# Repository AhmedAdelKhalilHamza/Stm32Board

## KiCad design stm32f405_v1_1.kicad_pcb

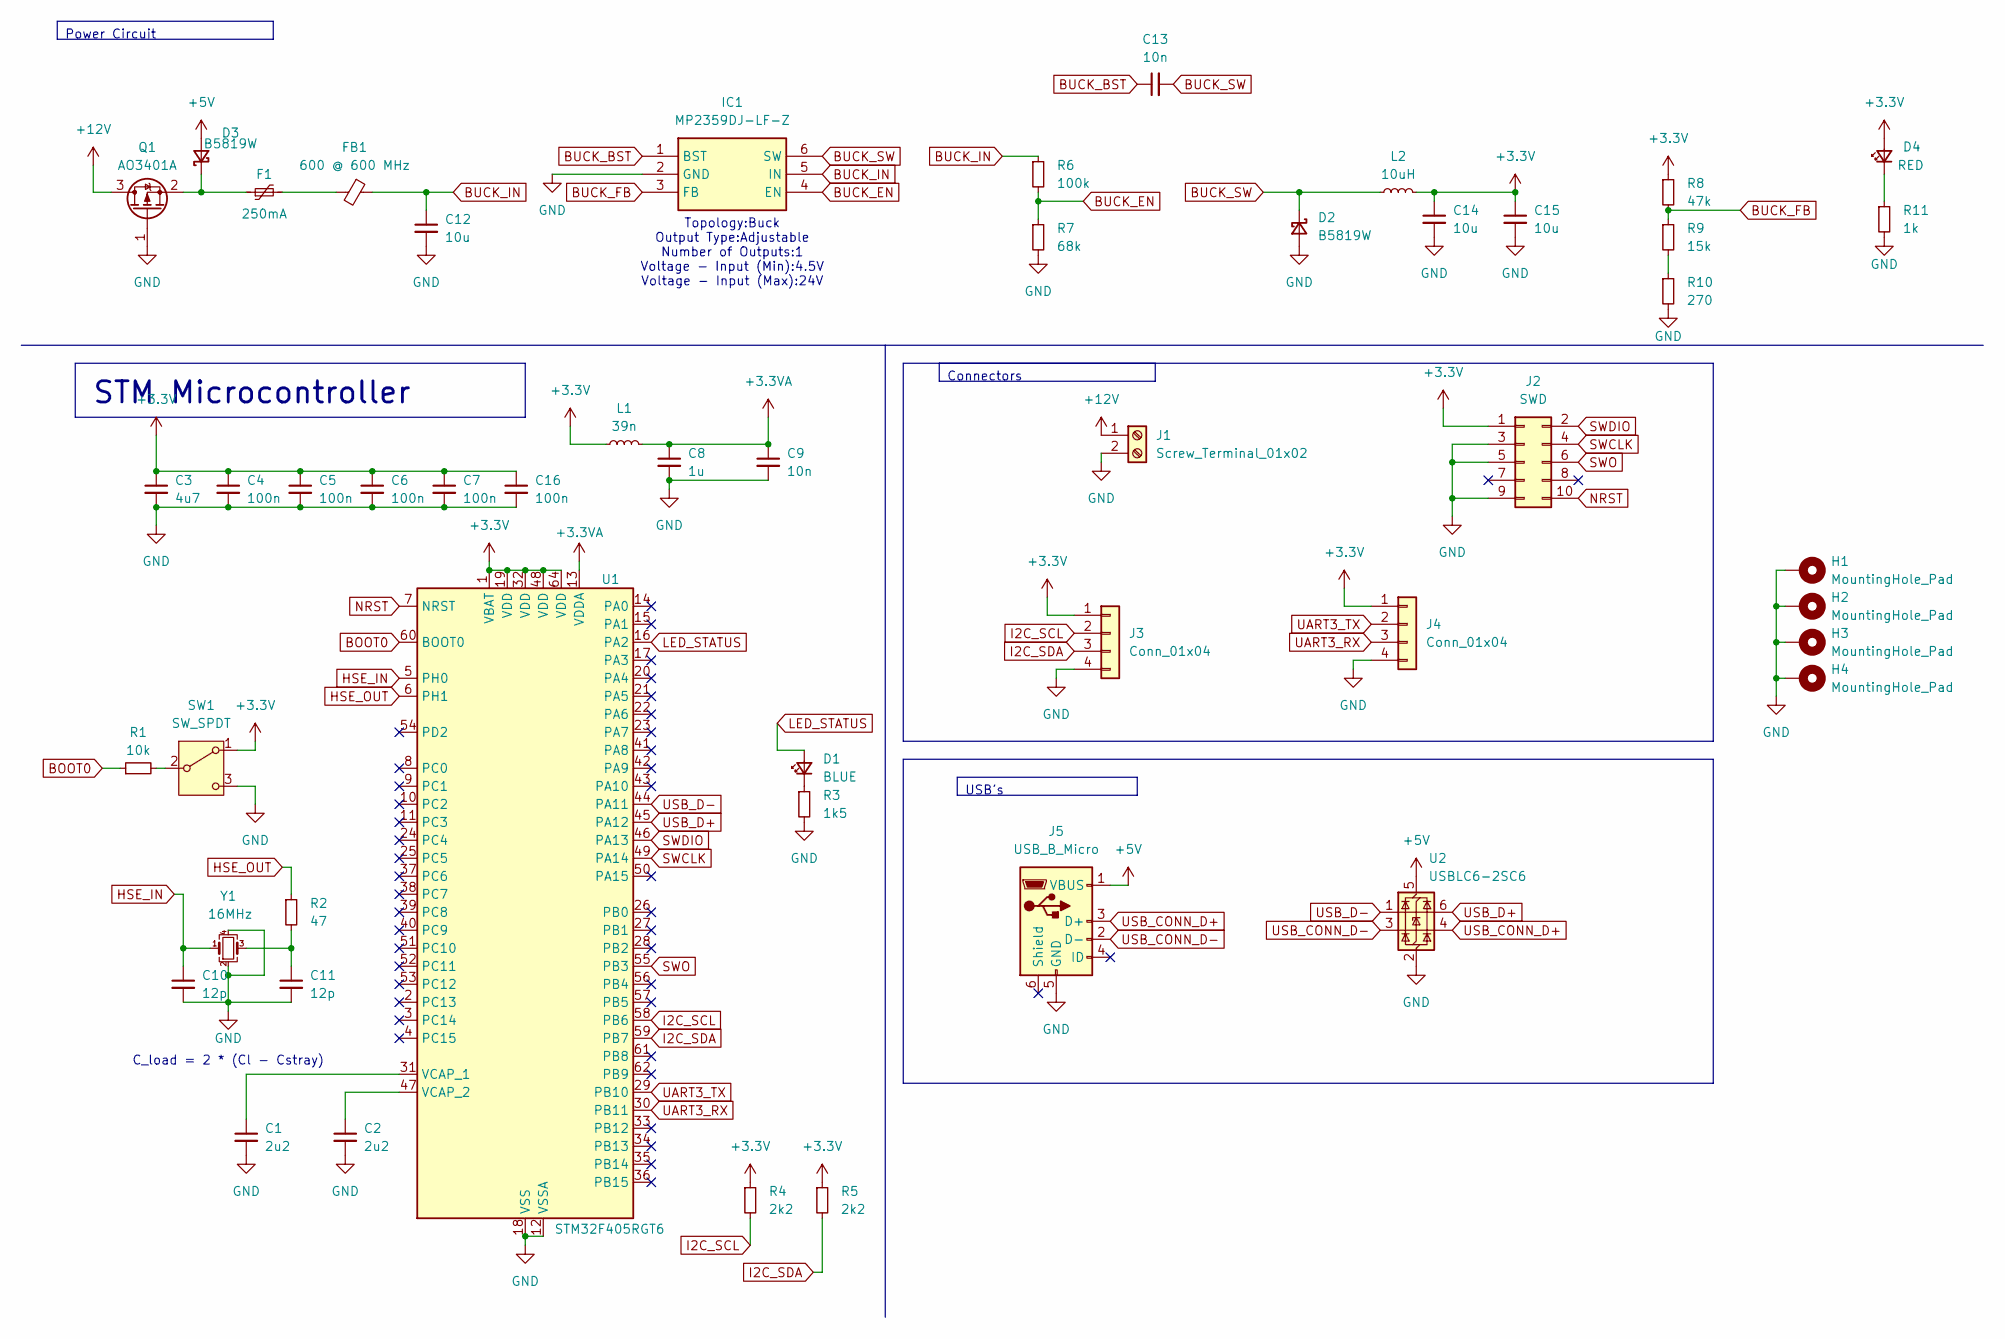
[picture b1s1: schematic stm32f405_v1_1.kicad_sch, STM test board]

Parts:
C1, C2: 2u2; C_0603_1608Metric; DigiKey# 1276-1134-1-ND
C3: 4u7; C_0603_1608Metric; DigiKey# 1276-1045-1-ND
C4, C5, C6, C7, C16: 100n; C_0402_1005Metric; DigiKey# 2679-AGC0402X7R160-104KNP-CT-ND
C8: 1u; C_0402_1005Metric; DigiKey# 490-13339-1-ND
C9: 10n; C_0402_1005Metric; DigiKey# 490-1313-1-ND
C10, C11: 12p; C_0402_1005Metric; DigiKey# 490-11190-1-ND
C12, C14, C15: 10u; C_1206_3216Metric; DigiKey# 1276-3105-1-ND
C13: 10n; C_0603_1608Metric; DigiKey# 399-C0603C103K9RAC7867CT-ND
D1: BLUE; LED_0603_1608Metric; DigiKey# 732-12013-1-ND
D2, D3: B5819W; D_SOD-123; DigiKey# 1727-7326-1-ND
D4: RED; LED_0603_1608Metric; DigiKey# 732-4978-1-ND
F1: 250mA; Fuse_1206_3216Metric; DigiKey# SF-1206HH25M-2CT-ND
FB1: 600 @ 600 MHz; L_0805_2012Metric; DigiKey# 1934-1435-1-ND
H1, H2, H3, H4: MountingHole_Pad; MountingHole_4.3mm_M4_Pad_Via
IC1: MP2359DJ-LF-Z; SOT95P280X100-6N; Manufacturer_Part_Number MP2359DJ-LF-Z; DigiKey# 1589-1889-1-ND
J1: Screw_Terminal_01x02; TerminalBlock_Phoenix_PT-1,5-2-3.5-H_1x02_P3.50mm_Horizontal; DigiKey# 732-10955-ND
J2: SWD; PinSocket_2x05_P1.27mm_Vertical_SMD; DigiKey# 1528-5327-ND
J3, J4: Conn_01x04; Molex_KK-254_AE-6410-04A_1x04_P2.54mm_Vertical; Mouser Part Number 538-171856-4004
J5: USB_B_Micro; USB_Mini-B_Wuerth_65100516121_Horizontal; DigiKey# 732-2109-1-ND
L1: 39n; L_0402_1005Metric; DigiKey# 2035-1057-1-ND
L2: 10uH; L_Sunlord_MWSA0518S; DigiKey# 3442-MWSA0518S-100MTCT-ND
Q1: AO3401A; SOT-23; DigiKey# 785-1001-1-ND
R1: 10k; R_0402_1005Metric; DigiKey# 311-10KJRCT-ND
R2: 47; R_0402_1005Metric; DigiKey# RMCF0402JT47R0CT-ND
R3: 1k5; R_0603_1608Metric; DigiKey# P1.5KDCCT-ND
R4, R5: 2k2; R_0402_1005Metric; DigiKey# P2.20KLCT-ND
R6: 100k; R_0603_1608Metric; DigiKey# 311-100KHRCT-ND
R7: 68k; R_0603_1608Metric; DigiKey# P68.0KHCT-ND
R8: 47k; R_0603_1608Metric; DigiKey# P47.0KHCT-ND
R9: 15k; R_0603_1608Metric; DigiKey# P15KDBCT-ND
R10: 270; R_0603_1608Metric; DigiKey# 311-270GRCT-ND
R11: 1k; R_0603_1608Metric; DigiKey# RMCF0603FT1K00CT-ND
SW1: SW_SPDT; SW_SPDT_PCM12; DigiKey# 401-2016-1-ND
U1: STM32F405RGT6; LQFP-64_10x10mm_P0.5mm; DigiKey# 497-11767-ND
U2: USBLC6-2SC6; SOT-23-6; DigiKey# 497-5235-1-ND
Y1: 16MHz; Crystal_SMD_3225-4Pin_3.2x2.5mm; DigiKey# 4983-12.88722CT-ND

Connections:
+3.3V: C3.1, C4.1, C5.1, C6.1, C7.1, C14.1, C15.1, C16.1, D4.2 (A), J2.1, J3.1, J4.1, L1.1, L2.2, R4.1, R5.1, R8.1, SW1.1 (A), U1.1 (VBAT), U1.19 (VDD), U1.32 (VDD), U1.48 (VDD), U1.64 (VDD)
+3.3VA: C8.1, C9.1, L1.2, U1.13 (VDDA)
+5V: D3.2 (A), J5.1 (VBUS), U2.5 (VBUS)
+12V: J1.1, Q1.3 (D)
BOOT0: R1.1, U1.60 (BOOT0)
BUCK_BST: C13.1, IC1.1 (BST)
BUCK_EN: IC1.4 (EN), R6.2, R7.1
BUCK_FB: IC1.3 (FB), R8.2, R9.1
BUCK_IN: C12.1, FB1.1, IC1.5 (IN), R6.1
BUCK_SW: C13.2, D2.1 (K), IC1.6 (SW), L2.1
GND: C1.2, C2.2, C3.2, C4.2, C5.2, C6.2, C7.2, C8.2, C9.2, C10.2, C11.2, C12.2, C14.2, C15.2, C16.2, D2.2 (A), H1.1, H2.1, H3.1, H4.1, IC1.2 (GND), J1.2, J2.3, J2.5, J2.9, J3.4, J4.4, J5.5 (GND), Q1.1 (G), R3.2, R7.2, R10.2, R11.2, SW1.3 (C), U1.12 (VSSA), U1.18 (VSS), U1.63 (VSS), U2.2 (GND), Y1.2, Y1.4
HSE_IN: C10.1, U1.5 (PH0), Y1.1
HSE_OUT: R2.1, U1.6 (PH1)
I2C_SCL: J3.2, R4.2, U1.58 (PB6)
I2C_SDA: J3.3, R5.2, U1.59 (PB7)
LED_STATUS: D1.2 (A), U1.16 (PA2)
NRST: J2.10, U1.7 (NRST)
unnamed: C11.1, R2.2, Y1.3
unnamed: D1.1 (K), R3.1
unnamed: D3.1 (K), F1.1, Q1.2 (S)
unnamed: D4.1 (K), R11.1
unnamed: F1.2, FB1.2
unnamed: R9.2, R10.1
unnamed: R1.2, SW1.2 (B)
unnamed: C1.1, U1.31 (VCAP_1)
unnamed: C2.1, U1.47 (VCAP_2)
SWCLK: J2.4, U1.49 (PA14)
SWDIO: J2.2, U1.46 (PA13)
SWO: J2.6, U1.55 (PB3)
UART3_RX: J4.3, U1.30 (PB11)
UART3_TX: J4.2, U1.29 (PB10)
USB_CONN_D+: J5.3 (D+), U2.4 (I/O2)
USB_CONN_D-: J5.2 (D-), U2.3 (I/O2)
USB_D+: U1.45 (PA12), U2.6 (I/O1)
USB_D-: U1.44 (PA11), U2.1 (I/O1)

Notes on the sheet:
Connectors
USB's
STM Microcontroller
Power Circuit
C_load = 2 * (Cl - Cstray)
Topology:Buck Output Type:Adjustable Number of Outputs:1 Voltage - Input (Min):4.5V Voltage - Input (Max):24V

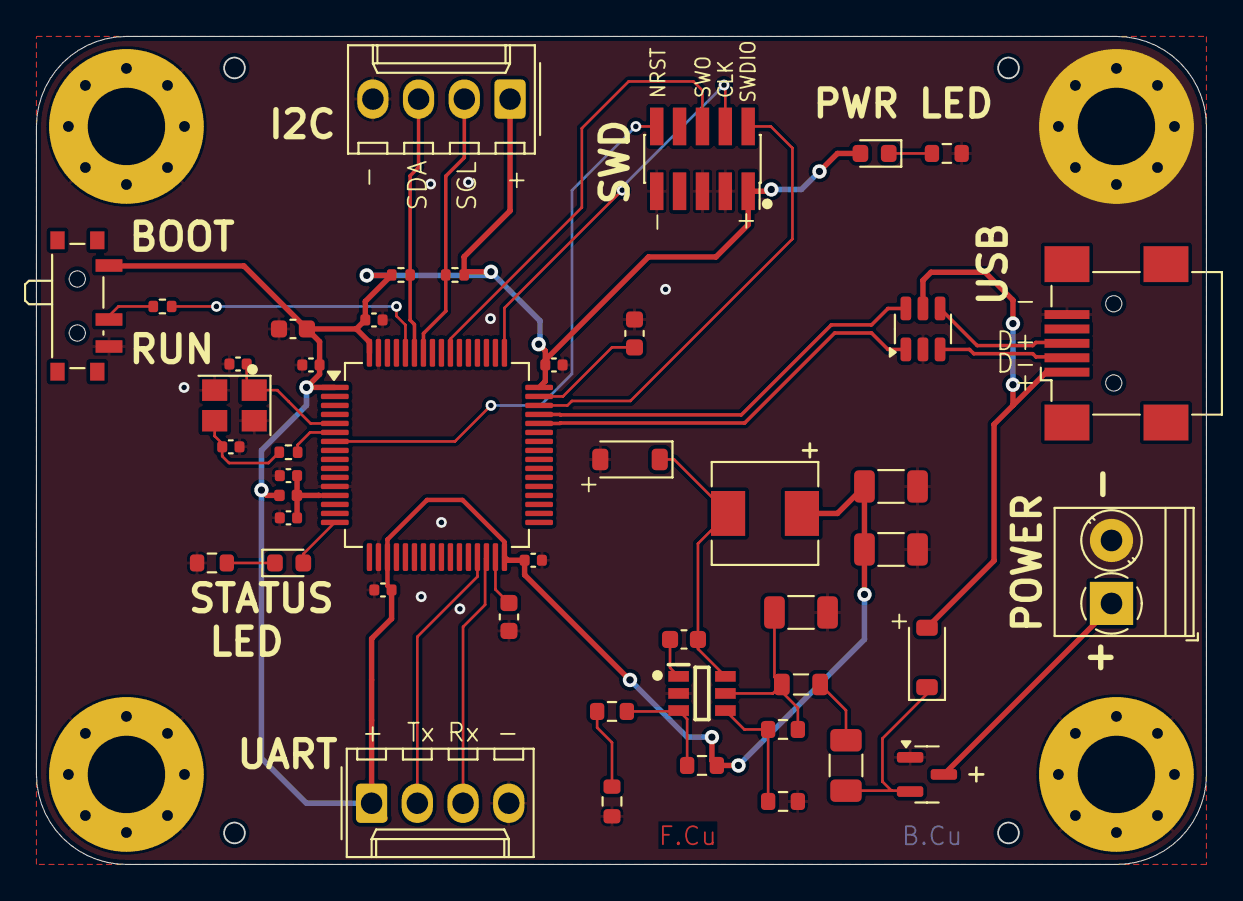
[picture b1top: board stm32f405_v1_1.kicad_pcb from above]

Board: 4 copper layers, 65.0 x 46.0 mm, 50 parts (0 on the bottom side), 35 nets.

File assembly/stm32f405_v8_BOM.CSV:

"Reference","Value","Datasheet","Footprint","Qty","DNP","#","Mouser Part Number","DigiKey MFR#","DigiKey#","Mouser MFR#"
"J3,J4","Conn_01x04","~","Connector_Molex:Molex_KK-254_AE-6410-04A_1x04_P2.54mm_Vertical","2","","1","538-171856-4004","","","171856-4004"
"Y1","16MHz","~","Crystal:Crystal_SMD_3225-4Pin_3.2x2.5mm","1","","2","","12.88722","4983-12.88722CT-ND",""
"J2","SWD","~","Connector_PinSocket_1.27mm:PinSocket_2x05_P1.27mm_Vertical_SMD","1","","3","","5327","1528-5327-ND",""
"J5","USB_B_Micro","~","Connector_USB:USB_Mini-B_Wuerth_65100516121_Horizontal","1","","4","","65100516121","732-2109-1-ND",""
"J1","Screw_Terminal_01x02","~","TerminalBlock_Phoenix:TerminalBlock_Phoenix_PT-1,5-2-3.5-H_1x02_P3.50mm_Horizontal","1","","5","","691137710002","732-10955-ND",""
"C9,C13","10n","~","-- mixed values --","2","","6","","-- mixed values --","-- mixed values --",""
"L1","39n","~","Inductor_SMD:L_0402_1005Metric","1","","7","","0402HM-390EGTS","2035-1057-1-ND",""
"D1","BLUE","~","LED_SMD:LED_0603_1608Metric","1","","8","","150060BS55040","732-12013-1-ND",""
"D4","RED","~","LED_SMD:LED_0603_1608Metric","1","","9","","150060RS75000","732-4978-1-ND",""
"C4,C5,C6,C7,C16","100n","~","Capacitor_SMD:C_0402_1005Metric","5","","10","","AGC0402X7R160-104KNP-CT","2679-AGC0402X7R160-104KNP-CT-ND",""
"D2,D3","B5819W","~","Diode_SMD:D_SOD-123","2","","11","","BAT46GWJ","1727-7326-1-ND",""
"C3","4u7","~","Capacitor_SMD:C_0603_1608Metric","1","","12","","CL10A475KQ8NNNC","1276-1045-1-ND",""
"C1,C2","2u2","~","Capacitor_SMD:C_0603_1608Metric","2","","13","","CL10B225KP8NNNC","1276-1134-1-ND",""
"C12,C14,C15","10u","~","Capacitor_SMD:C_1206_3216Metric","3","","14","","CL31B106KOHNNWE","1276-3105-1-ND",""
"R3","1k5","~","Resistor_SMD:R_0603_1608Metric","1","","15","","ERA-2AEB152X","P1.5KDCCT-ND",""
"R9","15k","~","Resistor_SMD:R_0603_1608Metric","1","","16","","ERA-3AEB153V","P15KDBCT-ND",""
"R4,R5","2k2","~","Resistor_SMD:R_0402_1005Metric","2","","17","","ERJ-2RKF2201X","P2.20KLCT-ND",""
"FB1","600 @ 600 MHz","~","Inductor_SMD:L_0805_2012Metric","1","","18","","FERRITE BEAD 100 OHM 0805 1LN","1934-1435-1-ND",""
"C10,C11","12p","~","Capacitor_SMD:C_0402_1005Metric","2","","19","","GJM1555C1H120FB01D","490-11190-1-ND",""
"C8","1u","~","Capacitor_SMD:C_0402_1005Metric","1","","20","","GRM155R70J105KA12J","490-13339-1-ND",""
"Q1","AO3401A","http://www.aosmd.com/pdfs/datasheet/AO3401A.pdf","Package_TO_SOT_SMD:SOT-23","1","","21","","MOSFET P-CH 30V 4A SOT23-3L","785-1001-1-ND",""
"IC1","MP2359DJ-LF-Z","https://datasheet.datasheetarchive.com/originals/distributor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","mp2359:SOT95P280X100-6N","1","","22","","MP2359DJ-LF-Z","1589-1889-1-ND",""
"L2","10uH","~","Inductor_SMD:L_Sunlord_MWSA0518S","1","","23","","MWSA0518S-100MT","3442-MWSA0518S-100MTCT-ND",""
"SW1","SW_SPDT","~","Button_Switch_SMD:SW_SPDT_PCM12","1","","24","","PCM12SMTR","401-2016-1-ND",""
"R1","10k","~","Resistor_SMD:R_0402_1005Metric","1","","25","","RC0402JR-0710KL","311-10KJRCT-ND",""
"R6","100k","~","Resistor_SMD:R_0603_1608Metric","1","","26","","RC0603FR-07100KL","311-100KHRCT-ND",""
"R10","270","~","Resistor_SMD:R_0603_1608Metric","1","","27","","RC0603JR-07270RL","311-270GRCT-ND",""
"R8","47k","~","Resistor_SMD:R_0603_1608Metric","1","","28","","RES SMD 47K OHM 1% 1/10W 0603","P47.0KHCT-ND",""
"R7","68k","~","Resistor_SMD:R_0603_1608Metric","1","","29","","RES SMD 68K OHM 1% 1/10W 0603","P68.0KHCT-ND",""
"R2","47","~","Resistor_SMD:R_0402_1005Metric","1","","30","","RMCF0402JT47R0","RMCF0402JT47R0CT-ND",""
"R11","1k","~","Resistor_SMD:R_0603_1608Metric","1","","31","","RMCF0603FT1K00","RMCF0603FT1K00CT-ND",""
"F1","250mA","~","Fuse:Fuse_1206_3216Metric","1","","32","","SF-1206HH25M-2","SF-1206HH25M-2CT-ND",""
"U1","STM32F405RGT6","https://www.st.com/resource/en/datasheet/stm32f405rg.pdf","Package_QFP:LQFP-64_10x10mm_P0.5mm","1","","33","","STM32F405RGT6","497-11767-ND",""
"U2","USBLC6-2SC6","https://www.st.com/resource/en/datasheet/usblc6-2.pdf","Package_TO_SOT_SMD:SOT-23-6","1","","34","","USBLC6-2SC6","497-5235-1-ND",""
